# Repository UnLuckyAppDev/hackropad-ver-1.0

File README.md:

# hackropad-ver-1.0
This github repo has all the files I used to make a macropad for the average Hackclub user. My macropad contains an OLED and a 3x3 keypad.

The following is a schematic made on KiCAD. 

The following is the PCB made on KiCAD.

The following image is the final assembled version (CAD not the real one, I will update my readme.md once I finish building the actual Hackropad).

The following is the BOM for the Hackropad

[Hack_Club_Macropad.csv](https://github.com/user-attachments/files/30129260/Hack_Club_Macropad.csv)

The following is a table of what the BOM is:
|Reference                          |Qty|Value                |Footprint                                                         |
|-----------------------------------|---|---------------------|------------------------------------------------------------------|
|D1,D2,D3,D4,D5,D6,D7,D8,D9         |9  |D                    |Diode_THT:D_DO-41_SOD81_P7.62mm_Horizontal                        |
|SW1,SW2,SW3,SW4,SW5,SW6,SW7,SW8,SW9|9  |SW_Push              |Button_Switch_Keyboard:SW_Cherry_MX_1.00u_PCB                     |
|U1                                 |1  |MOUDLE-SEEEDUINO-XIAO|HackClub KiCAD Care Package:XIAO-Generic-Hybrid-14P-2.54-21X17.8MM|
|U2                                 |1  |ER_OLEDM0.91_1x-I2C  |Display:ER_OLEDM0.91_1x-I2C                                       |

The D is the diode, sw push are the keys, and U1 is the Moudle Seeduino Xiao (the main MCU), the U2 is the OLED.

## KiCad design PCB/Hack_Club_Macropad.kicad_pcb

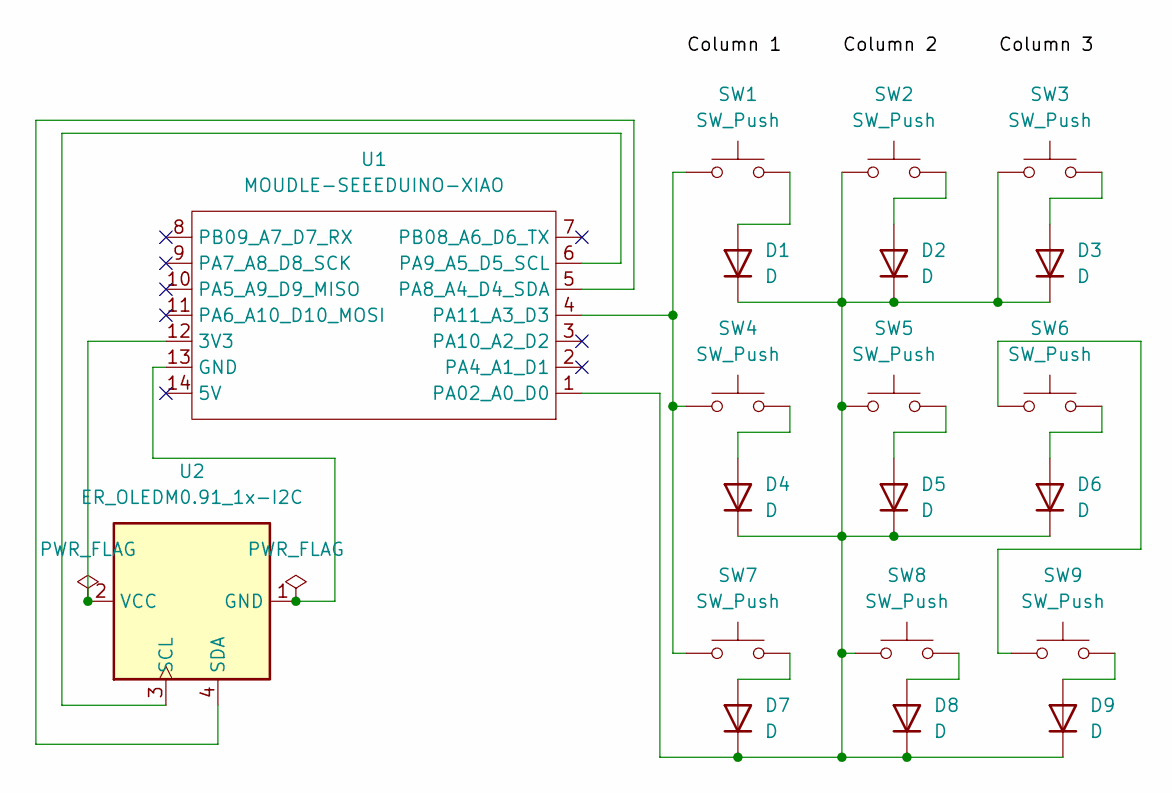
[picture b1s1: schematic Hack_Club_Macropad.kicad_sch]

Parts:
D1, D2, D3, D4, D5, D6, D7, D8, D9: D; D_DO-41_SOD81_P7.62mm_Horizontal
SW1, SW2, SW3, SW4, SW5, SW6, SW7, SW8, SW9: SW_Push; SW_Cherry_MX_1.00u_PCB
U1: MOUDLE-SEEEDUINO-XIAO; XIAO-Generic-Hybrid-14P-2.54-21X17.8MM
U2: ER_OLEDM0.91_1x-I2C

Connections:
unnamed: D1.2 (A), SW1.2
unnamed: D1.1 (K), D2.1 (K), D3.1 (K), D4.1 (K), D5.1 (K), D6.1 (K), D7.1 (K), D8.1 (K), D9.1 (K), SW2.1, SW3.1, SW5.1, SW8.1, U1.1 (PA02_A0_D0)
unnamed: D2.2 (A), SW2.2
unnamed: D3.2 (A), SW3.2
unnamed: D4.2 (A), SW4.2
unnamed: D5.2 (A), SW5.2
unnamed: D6.2 (A), SW6.2
unnamed: D7.2 (A), SW7.2
unnamed: D8.2 (A), SW8.2
unnamed: D9.2 (A), SW9.2
unnamed: SW6.1, SW9.1
unnamed: U1.12 (3V3), U2.2 (VCC)
unnamed: U1.13 (GND), U2.1 (GND)
unnamed: U1.5 (PA8_A4_D4_SDA), U2.4 (SDA)
unnamed: U1.6 (PA9_A5_D5_SCL), U2.3 (SCL)
unnamed: SW1.1, SW4.1, SW7.1, U1.4 (PA11_A3_D3)

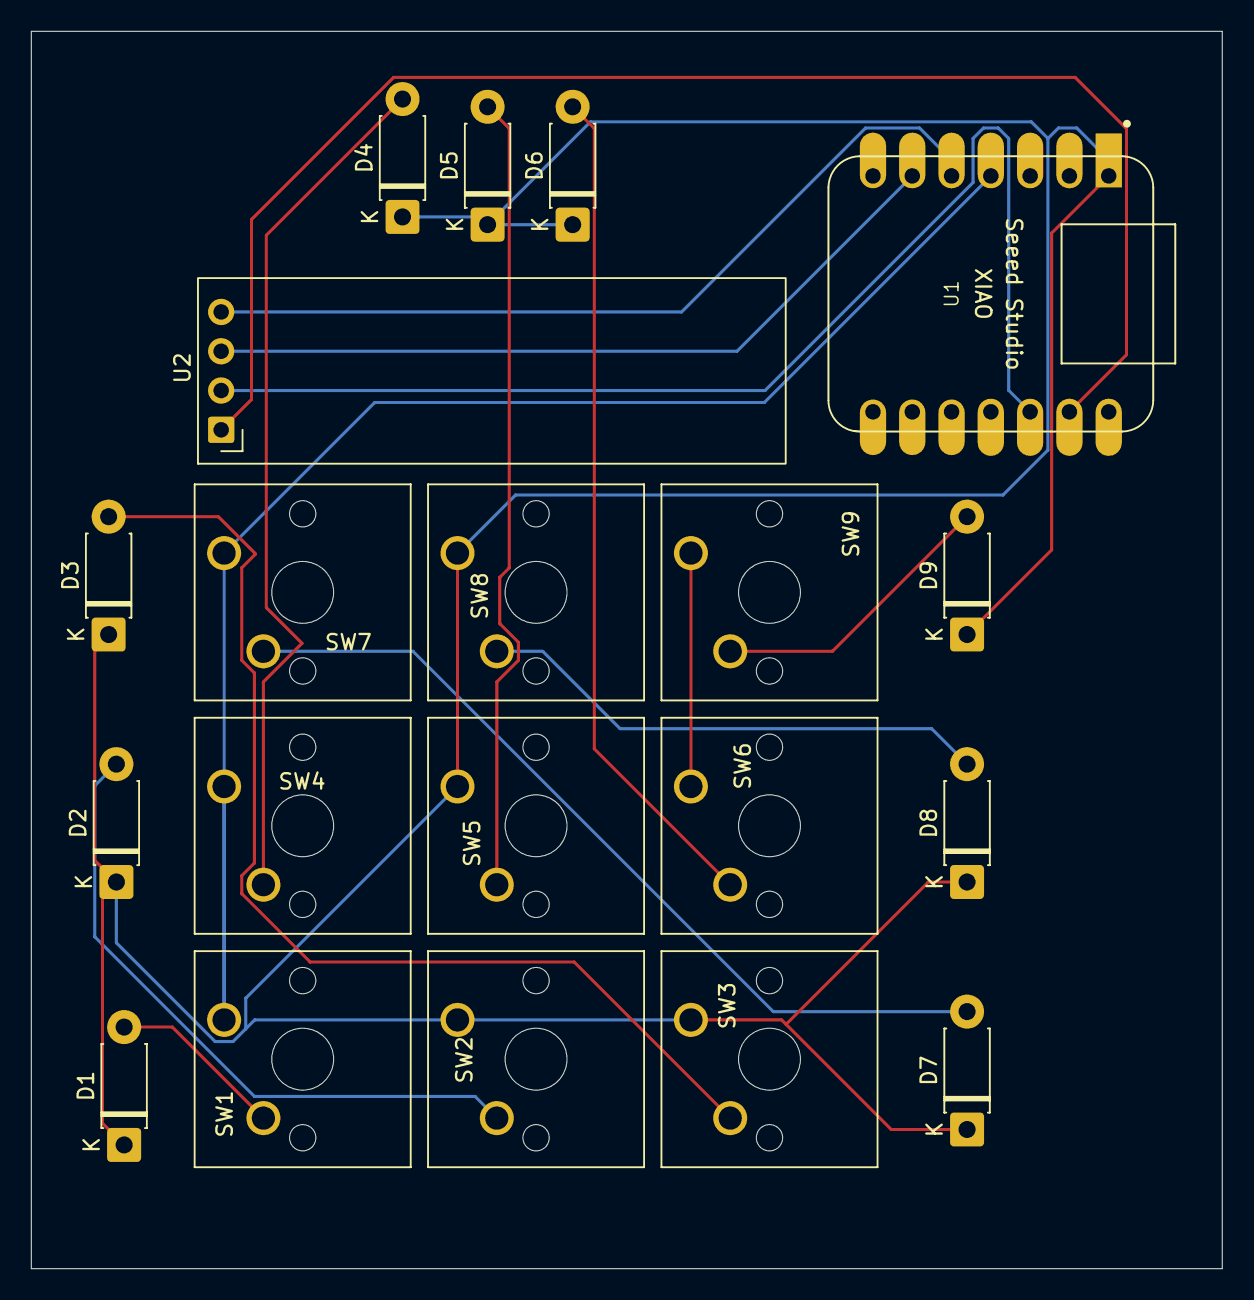
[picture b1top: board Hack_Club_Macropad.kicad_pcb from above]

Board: 2 copper layers, 77.0 x 80.0 mm, 20 parts (0 on the bottom side), 16 nets.

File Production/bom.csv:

"Reference","Qty","Value","Exclude from Board","Footprint"
"D1,D2,D3,D4,D5,D6,D7,D8,D9","9","D","","Diode_THT:D_DO-41_SOD81_P7.62mm_Horizontal"
"SW1,SW2,SW3,SW4,SW5,SW6,SW7,SW8,SW9","9","SW_Push","","Button_Switch_Keyboard:SW_Cherry_MX_1.00u_PCB"
"U1","1","MOUDLE-SEEEDUINO-XIAO","","HackClub KiCAD Care Package:XIAO-Generic-Hybrid-14P-2.54-21X17.8MM"
"U2","1","ER_OLEDM0.91_1x-I2C","","Display:ER_OLEDM0.91_1x-I2C"
